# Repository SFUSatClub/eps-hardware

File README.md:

# CubeSat Electrical Power Subsystem
KiCad project of the cubesat electrical power subsystem test article in preparation for the Canadian Satellite Design Challenge

This repository uses the SFU Satellite Team's KiCad component library as a submodule.
To start working on the repository:

```
1. Open the git shell
2. Navigate to the directory you wish to place the repository inside
3. git clone --recursive "https://github.com/SFUSatClub/eps-hardware.git"
4. cd .\eps-hardware\KiCad-Lib\
5. git checkout master
```

If you modify either the component schematic or footprint libraries you must push those changes to the SFUSatClub/KiCad-Lib repository.

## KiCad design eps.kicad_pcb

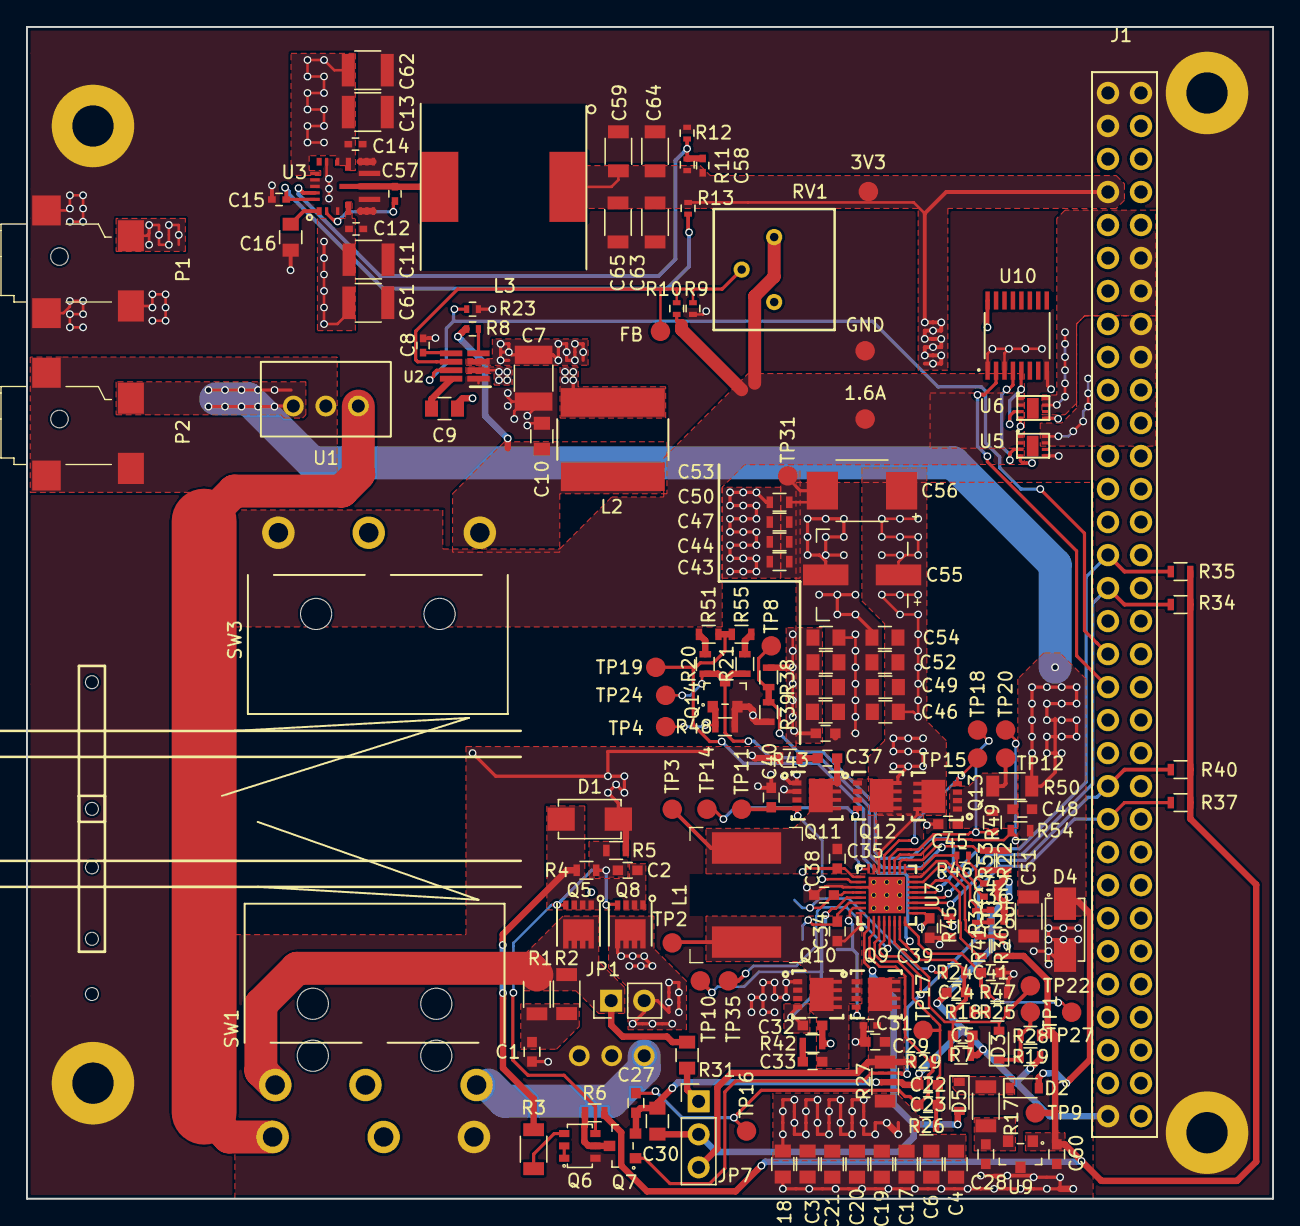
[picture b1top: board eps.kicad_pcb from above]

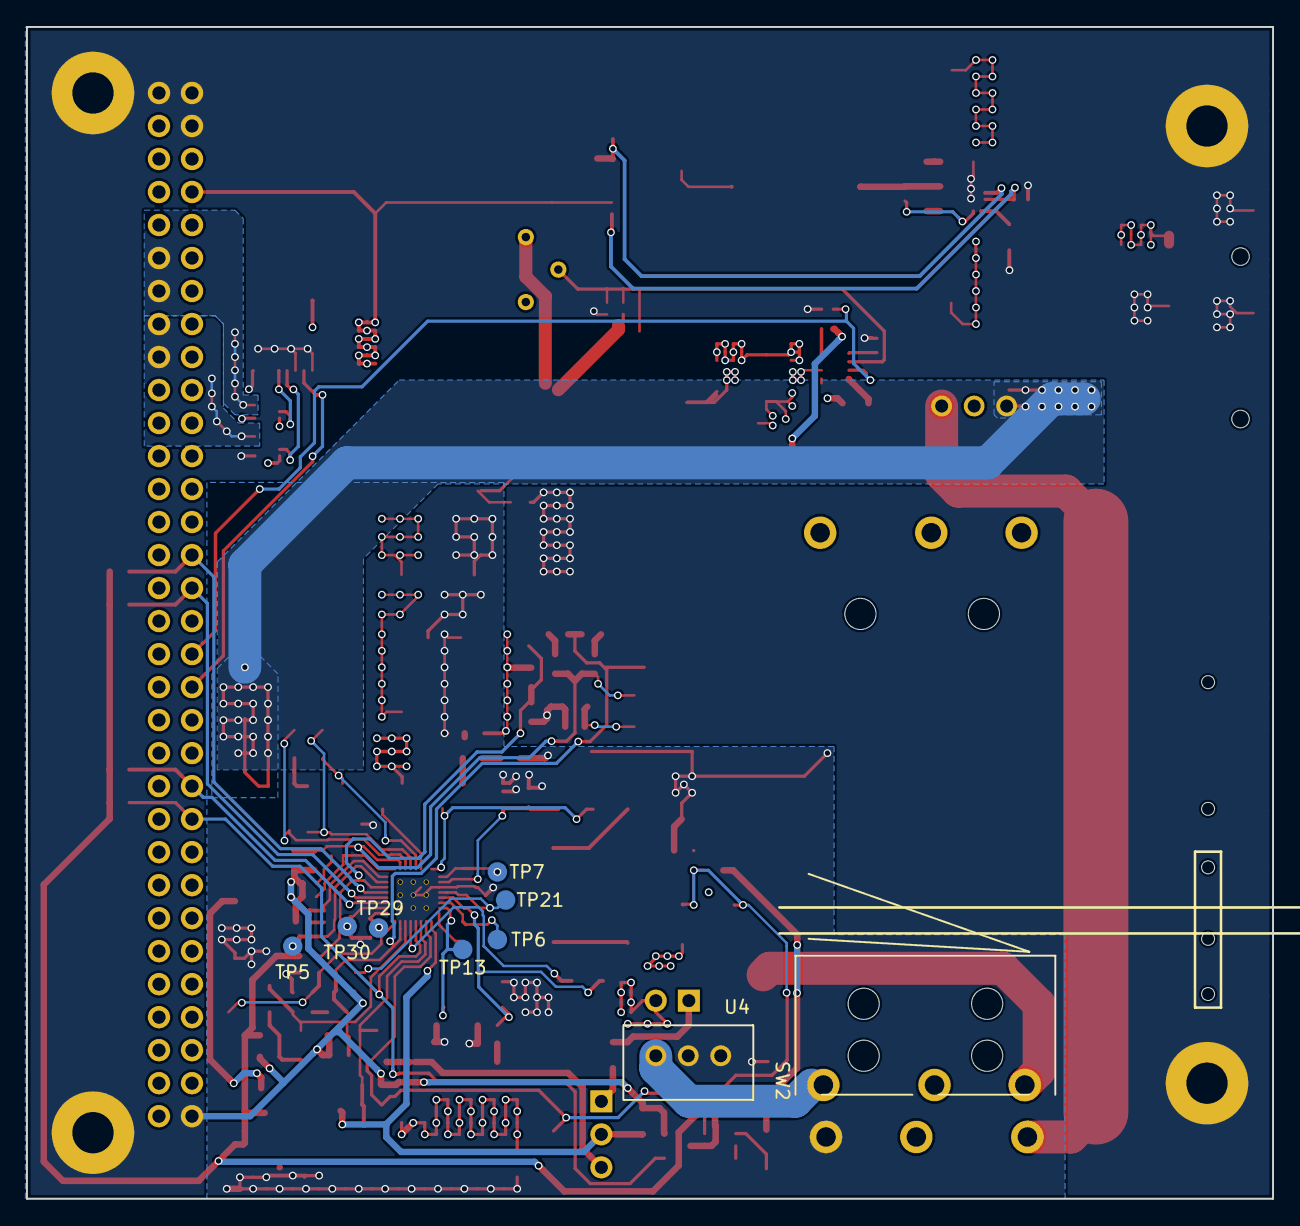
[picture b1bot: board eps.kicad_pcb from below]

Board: 4 copper layers, 95.9 x 90.2 mm, 189 parts (9 on the bottom side), 80 nets.

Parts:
C1, C24: 1u0; C_0603
C2, C28, C48, C60: 100n0; C_0603
C3, C18, C53, C54: DNP; C_0805
C4, C6, C17, C19, C20, C21: 10u0; C_0805
C5, C39, C41: 100p0; C_0603
C7: 22.0 uF; C_1210
C8: 8.2 nF; C_0402
C9: 100.0 nF; C_0805
C10: 47.0 uF; C_0805
C11, C13, C61, C62: 10.0 uF; C_1210
C12, C14: 1.0 nF; C_0402
C15: 100.0 nF; C_0402
C16: 4.7 uF; C_0805
C22, C27: 33n0; C_0603
C23, C33, C37, C43: DNP; C_0603
C25: 33p0; C_0402
C26: 1n8; C_0402
C29: 10n0; C_0603
C30: 470n0; C_0805
C31: 1n0; C_0402
C32, C40: 150p; C_0603
C34, C35: 47n; C_0603
C36: 15p0; C_0402
C38: 2u2; C_0603
C42: 680p; C_0402
C44, C46, C47, C49, C50, C52: 10u; C_0805
C45: 1u; C_0603
C51: 10u0; C_1206
C55: DNP; C_ALUM_2626
C56: 47u; C_TANT_2917
C57: 470.0 nF; C_0402
C58: 680.0 pF; C_0402
C59, C63, C64, C65: 68.0 uF; C_1206
D1: SMAJ26CA; DO-214AC-BI
D2, D3, D5: BAT54HT1G; SOD-323
D4: B220A-13-F; DO-214AC
J1: PC104-8BIT; PC104-8bit
J2, J3, J4, J5: PC104PTH
JP1: Conn_01x02; Socket_Strip_Straight_1x02_Pitch2.54mm
JP7: Conn_01x03; Socket_Strip_Straight_1x03_Pitch2.54mm
L1: 2u2; L_8030
L2: 2.2 uH; SRN8040-2R2Y
L3: 10.0 uH; L_7447709100
P1, P2: 3pin-DC-power; PJ-028-SMT-TR-3pin-DC-jack
Q5, Q8: DMP3035SFG-7; POWERDI3333-8
Q6: DCX124EK-7-F; SC-74
Q7, Q14: 2N7002ET1G; SOT-23-3
Q9, Q10, Q11, Q12: CSD17551Q3A; 8-PowerWDFN
Q13: CSD25402Q3A; 8-PowerWDFN
R1, R2: 3R9; R_1206
R3, R17: 10R0; R_1206
R4, R53: 100k0; R_0603
R5: 20k0; R_0603
R6, R36, R37, R40: 10k0; R_0603
R7: 220k0; R_0603
R8: 100k; R_0402
R9: DNP; R_0402
R10: 1k62; R_0402
R11: 49.9 kOhm; R_0402
R12: 21.5 kOhm; R_0402
R13: 3.01 Ohm; R_0402
R14, R15, R16, R19, R21, R22, R34, R35, R38, R42, R43, R44: DNP; R_0603
R18, R20: 0R; R_0603
R23: 1K; R_0402
R24, R49, R54: 10R0; R_0603
R25, R28: 383k0; R_0603
R26, R29: 4R99; R_0603
R27, R50: 10m0; R_1206
R31: 1R0; R_0805
R32: 40k2; R_0402
R39, R48: 300k0; R_0603
R41: 2M0; R_0603
R45: 30k1; R_0603
R46: 10k0; R_0402
R47: 137k0; R_0603
R51: 120k0; R_0603
R55: 64k9; R_0603
RV1: CT6EP103
SW1, SW2: LIMIT_SWITCH; SS-3GLPD-L
SW3: LIMIT_SWITCH; SS-3GLPD-R
TP1, TP2, TP3, TP4, TP5, TP6, TP7, TP8, TP9, TP10, TP11, TP12, TP13, TP14, TP15, TP16, TP17, TP18, TP19, TP20, TP21, TP22, TP23, TP24, TP25, TP27, TP28, TP29, TP30, TP31, TP33, TP35: TEST; Measurement_Point_Round-SMD-Pad_Small
U1, U4: B3B-XH-A(LF)(SN); B3B-XH-A
U2: TPS563219DDFR-ND; SOT-23-8
U3: LMS3635AQRNLRQ1; LMS3635AQRNLTQ1
U5, U6: TPS22967
U7: bq25703arsnt; S-PWQFN-N32
U9: LM3480; SOT-23-3
U10: CD4555BPWR; TSSOP-16

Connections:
/1.6A_Regulator_PDB/1.6A: C10.1, L2.1, R8.2, SW3.COM
/1.6A_Regulator_PDB/PG: R8.1, U2.4
/1.6A_Regulator_PDB/SW: C9.1, L2.2, U2.2
/1.6A_Regulator_PDB/VBOOT: C9.2, U2.8
/3.3V_Regulator_PDB/BIAS: C15.1, R13.2, U3.22
/3.3V_Regulator_PDB/CBOOT: C57.1, U3.2
/3.3V_Regulator_PDB/FB: C58.2, R11.2, R12.1, U3.21
/3.3V_Regulator_PDB/SW: C57.2, L3.2, U3.9
/3.3V_Regulator_PDB/VCC: C16.1, U3.1
/3V3: C58.1, C59.1, C63.1, C64.1, C65.1, J1.3B, J1.29B, L3.1, R11.1, R13.1, TP28.1, U5.4, U6.4, U10.16
/+z_rail: J1.24A, J1.25A, U5.7, U5.8
/-z_rail: J1.26A, J1.27A, U6.7, U6.8
/BMS/3V3: C60.1, R6.1, R28.1, R34.1, R35.1, R36.1, R37.1, R40.1, TP9.1, U9.1
/BMS/ACN: C23.2, C27.1, R29.2, TP16.1, U7.2
/BMS/ACP: C22.1, C23.1, R26.2, TP17.1, U7.3
/BMS/CELL_control: Q14.1, R48.2, TP4.1
/BMS/COMP2: C36.1, R46.1, U7.17
/BMS/HIDRV1: Q9.4, TP13.1, U7.31
/BMS/HIDRV2: Q12.4, TP14.1, U7.24
/BMS/ILIM_HIZ: C5.1, D3.1, R7.1, R25.1, TP22.1, U7.6
/BMS/ILIM_control: D3.2, R19.1, R28.2, TP1.1
/BMS/LODRV1: C32.1, Q10.4, TP10.1, U7.29
/BMS/LODRV2: C40.1, Q11.4, TP11.1, U7.26
/BMS/REGN: C38.1, R24.1, TP21.1, U7.28
/BMS/SRN: R54.2, TP20.1, U7.19
/BMS/SRP: R49.2, TP18.1, U7.20
/BMS/SW1: C33.1, C34.1, L1.1, Q9.1, Q9.2, Q9.3, Q10.5, Q10.6, Q10.7, Q10.8, Q10.9, TP2.1, U7.32
/BMS/SW2: C35.1, C37.1, L1.2, Q11.5, Q11.6, Q11.7, Q11.8, Q11.9, Q12.1, Q12.2, Q12.3, TP3.1, U7.23
/BMS/VBUS: C30.1, D5.1, JP7.2, U7.1
/BMS/VDDA: C24.1, R18.1, R24.2, R51.2, R55.2, TP19.1, U7.7
/BMS/VIN+: JP1.1, Q5.5, Q5.6, Q5.7, Q5.8, Q5.9, R1.1, R2.1, R31.2, SW1.NC
/CHG_OK: J1.10B, Q7.1, R37.2, U7.4
/DPL_EN: J1.15B, R23.1, U2.7
/DPL_SEL: J1.14B, U10.2
/FB: R9.2, R10.1, RV1.2, TP23.1, U2.6
/PowerDistributionDeploymentControl/1.6A: R9.1, RV1.1, SW3.NC, TP25.1, U5.1, U5.2, U6.1, U6.2
/PowerDistributionDeploymentControl/on+z: U5.3, U10.4
/PowerDistributionDeploymentControl/on-z: U6.3, U10.5
/SCL: J1.18B, R35.2, U7.13
/SDA: J1.17B, R34.2, U7.12
/VSYS_RETURN: C7.1, C11.1, C12.1, C13.1, C14.1, C61.1, C62.1, J1.28A, J1.29A, P1.1, U2.3, U3.4, U3.14, U3.15, U3.18
/VSYS_UP: C43.1, C44.1, C46.1, C47.1, C49.1, C50.1, C52.1, C53.1, C54.1, C55.1, C56.1, J1.30A, J1.31A, Q12.5, Q12.6, Q12.7, Q12.8, Q12.9, Q13.5, Q13.6, Q13.7, Q13.8, Q13.9, R38.1, U7.22
/Vin_Solar: SW1.COM, U4.3
/pack+: C48.2, C51.1, D2.1, D4.2, P2.1, R50.2, R54.1, U1.1
/pack-: P2.2, P2.3, U1.2
/return: SW2.COM, U1.3
/~PROCHP: J1.11B, R40.2, U7.11
GND: C5.2, C7.2, C8.2, C10.2, C11.2, C12.2, C13.2, C14.2, C15.2, C16.2, C22.2, C24.2, C25.1, C26.1, C27.2, C30.2, C36.2, C42.2, C59.2, C61.2, C62.2, C63.2, C64.2, C65.2, J1.1B, J1.31B, J1.32A, J1.32B, J2.1, J3.1, J4.1, J5.1, P1.2, P1.3, Q7.2, Q14.2, R7.2, R10.2, R12.2, R14.2, R15.2, R16.2, R19.2, R22.2, R23.2, R39.2, R44.2, R48.1, R53.1, TP33.1, U2.1, U3.3, U3.5, U3.6, U3.7, U3.8, U3.10, U3.11, U3.12, U3.13, U3.16, U3.19, U3.20, U5.5, U6.5, U10.1, U10.3, U10.8
GNDPWR: C1.2, C3.2, C4.2, C6.2, C17.2, C18.2, C19.2, C20.2, C21.2, C28.2, C29.2, C31.2, C32.2, C38.2, C39.2, C40.2, C41.2, C43.2, C44.2, C45.2, C46.2, C47.2, C49.2, C50.2, C51.2, C52.2, C53.2, C54.2, C55.2, C56.2, C60.2, D1.2, D4.1, Q6.6, Q10.1, Q10.2, Q10.3, Q11.1, Q11.2, Q11.3, R5.2, R14.1, R15.1, R16.1, R42.2, R43.2, R44.1, R45.1, R47.1, SW2.NC, TP31.1, U4.1, U4.2, U7.27, U7.33, U9.3
unnamed: C1.1, R1.2, R2.2
unnamed: C2.1, D1.1, Q5.1, Q5.2, Q5.3, Q8.1, Q8.2, Q8.3, R3.1, R4.1
unnamed: C2.2, Q5.4, Q6.4, Q8.4, R4.2, R5.1
unnamed: C8.1, U2.5
unnamed: C3.1, C4.1, C6.1, C17.1, C18.1, C19.1, C20.1, C21.1, JP1.2, Q8.5, Q8.6, Q8.7, Q8.8, Q8.9, R26.1, R27.1
unnamed: C25.2, R32.2, U7.16
unnamed: C26.2, R32.1
unnamed: C28.1, R17.2, U9.2
unnamed: C29.1, C31.1, JP7.3, Q9.5, Q9.6, Q9.7, Q9.8, Q9.9, R27.2, R29.1
unnamed: C33.2, R42.1
unnamed: C34.2, TP6.1, U7.30
unnamed: C35.2, TP7.1, U7.25
unnamed: C37.2, R43.1
unnamed: C39.1, TP29.1, U7.9
unnamed: C41.1, R47.2, TP27.1, U7.8
unnamed: C42.1, R46.2
unnamed: C45.1, C48.1, Q13.1, Q13.2, Q13.3, R49.1, R50.1, TP12.1
unnamed: D2.2, D5.2, R17.1
unnamed: JP7.1, R31.1
unnamed: Q6.1, Q6.2
unnamed: Q6.3, R3.2
unnamed: Q6.5, Q7.3, R6.2
unnamed: Q13.4, TP15.1, U7.21
unnamed: Q14.3, R20.2, R21.2, R22.1, R53.2, TP24.1, U7.18
unnamed: R18.2, R25.2
unnamed: R20.1, R51.1
unnamed: R21.1, R55.1
unnamed: R36.2, R41.1, TP5.1, U7.15
unnamed: R38.2, R39.1, R41.2, TP8.1, U7.14
unnamed: R45.2, TP30.1, U7.10
unnamed: TP35.1, U7.5

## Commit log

2017-09-04 MPPT schematic complete. Following ST app note AN3319 section 5.
2017-09-09 Updated README.md with correct file repo locations
2017-09-11 created MPPT hierarchical sheet
2017-09-11 added hierarchical sheet for BMS
2017-09-11 copied MPPT section for each of 4 side panels. The name for these 4 panels should be more descriptive
2017-09-12 overvoltage protection, charging/discharging fets, coloumb counter filter schematics complete. What should the secondary overvoltage output trigger? How should the MPPT output connect to the battery 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
2018-01-23 Started adding BQ25703ARSNT
2018-01-23 Updating library
2018-01-23 Fixed paste layer generation error. The global paste clearance layer set to -0.1mm cause some pads to not have a paste aperture generated in gerbers.
2018-02-05 Deleted MPPT curcuit. MPPT has been transfered to the panel-connector board
2018-02-06 Seriously starting the BMS schematic
2018-02-09 Continued BMS schematic updates
2018-02-12 Added aluminum 47u cap
2018-02-13 Added some more BMS components
2018-02-13 Added Schematic for Series battery pack with balancer
2018-02-13 Added schematic for the full 2s4p battery pack, added some of the components for the battery connection to the BMS
2018-02-14 Replaced battery symbol from the device library with one from SFUSat-Power
2018-02-16 Added more BMS-new components
2018-02-18 moved series battery symbol to SFUSat lib
2018-02-18 Continued BMS_new.sch work
2018-02-18 More BMS_new updates
2018-02-21 Pretty much done BMS_new
2018-02-21 Fixed output of BMS_new
2018-03-10 added DC jack and made 3d model
2018-03-10 added 3d models for the largest cap and inductor
2018-03-11 added deployment switches and DC jacks
2018-03-18 deleted batteries and changed BMS_new name
2018-03-25 Including PDB schematics and components for 3.3V and 1.6A regulators
2018-03-25 Seperated PCB Components into schematic format
2018-03-30 merged Power-Dist branch back onto master
2018-03-30 fixed rescue components and missing schematic issues
2018-03-30 cleaned up sheets and heirarchical pins. Also added test points and connectors to BMS scheet
2018-03-30 completed BMS schematic
2018-03-30 schematic complete
2018-03-30 i dont know what i changed
2018-03-31 moved libraries around. See commits in Kicad-Lib
2018-03-31 replaced 0.1inch jumpers with SMT jumpers, made board 4 layers
2018-04-01 Started laying out the components, spacings and positions are temporary most are just placed relative to their locations in the schematic
2018-04-01 fixed demultiplexer
2018-04-06 Fixed Miscellanious Errors in PDB Portion
    Fixed Inductor SER2915L and small issues with footprints and pins for
    PDB Components.
2018-04-06 Fixed TPS22964xC IC Pins
2018-04-06 Updated Netlist with New Footprints
2018-04-22 Placed the Power Distribution Circuits on the PCB
    Includes traces rated for 2A.
2018-04-22 Layed Out the Limit Switch Connections
    Inputs from limit switches for the BMS have been created and traced out.
    Only implementation left is the BMS then connections from the BUS
2018-04-27 Attempt 2 at laying out 3.3V and 1.6A PD
2018-04-27 Updated GND Layer
2018-04-28 Began BMS
2018-04-30 working on layout..
2018-05-02 Working on BQ25703a
2018-05-02 Working on BQ25703a, shrunk 1.6A regulator
2018-05-03 Bump KiCad-Lib
2018-05-03 Updataed demuxes on 1.6A distriution
2018-05-03 rearranged the 1.6A regulator to make it more compact, trying to get more space for BMS
2018-05-03 All the components are on the board, phew
2018-05-04 Finished layout, needs DRZ check and to be reviewed
2018-05-04 removed duplicate GND fill on bottom layer
2018-05-04 Split GND fills on Top and Bottom layers to match internal GND layer, fixed some fill priority issues, reduced some of the excessive vias :(.
2018-05-04 Fix pitch on U3 pins 5,6,12,13
2018-05-04 Fixed #8 and Fixed #14 officially and put correct footprints into layout. Needs to be fixed (specifically VSYS pin of the BMS needs to be connected)
2018-05-04 attempting to fix things
2018-05-05 imporved polygons, connected DPL_EN
2018-05-05 added pull down on deployment enable pin incase the OBC output is undefined
2018-05-05 Fix Q6 footprint and redo traces
2018-05-06 Fixed Q6 routing
2018-05-10 Fix switch footprint terminal spacing and adjust track ends accordingly
2018-05-10 Move pads closer together on C56 footprint
2018-05-11 Update D4 pad dimensions and spacing to patch datasheet, regenerate pours
2018-05-12 all nets connected
2018-05-12 resolved fill related errors
2018-05-12 reanamed nets to make layout easier
2018-05-12 removed reduendent polygon
2018-05-14 improved high current traces
2018-05-16 added adjustible feedback for 1.6 a regulator. The point where the feedback taps off moved to after the RBF switch for better control
2018-05-16 simplified polygons, added holes for pin guides, added testpoints for power nets
2018-05-16 modified FB pot config

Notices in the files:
parts and their libraries:
Copyright 2016 Accelerated Designs. All rights reserved.
